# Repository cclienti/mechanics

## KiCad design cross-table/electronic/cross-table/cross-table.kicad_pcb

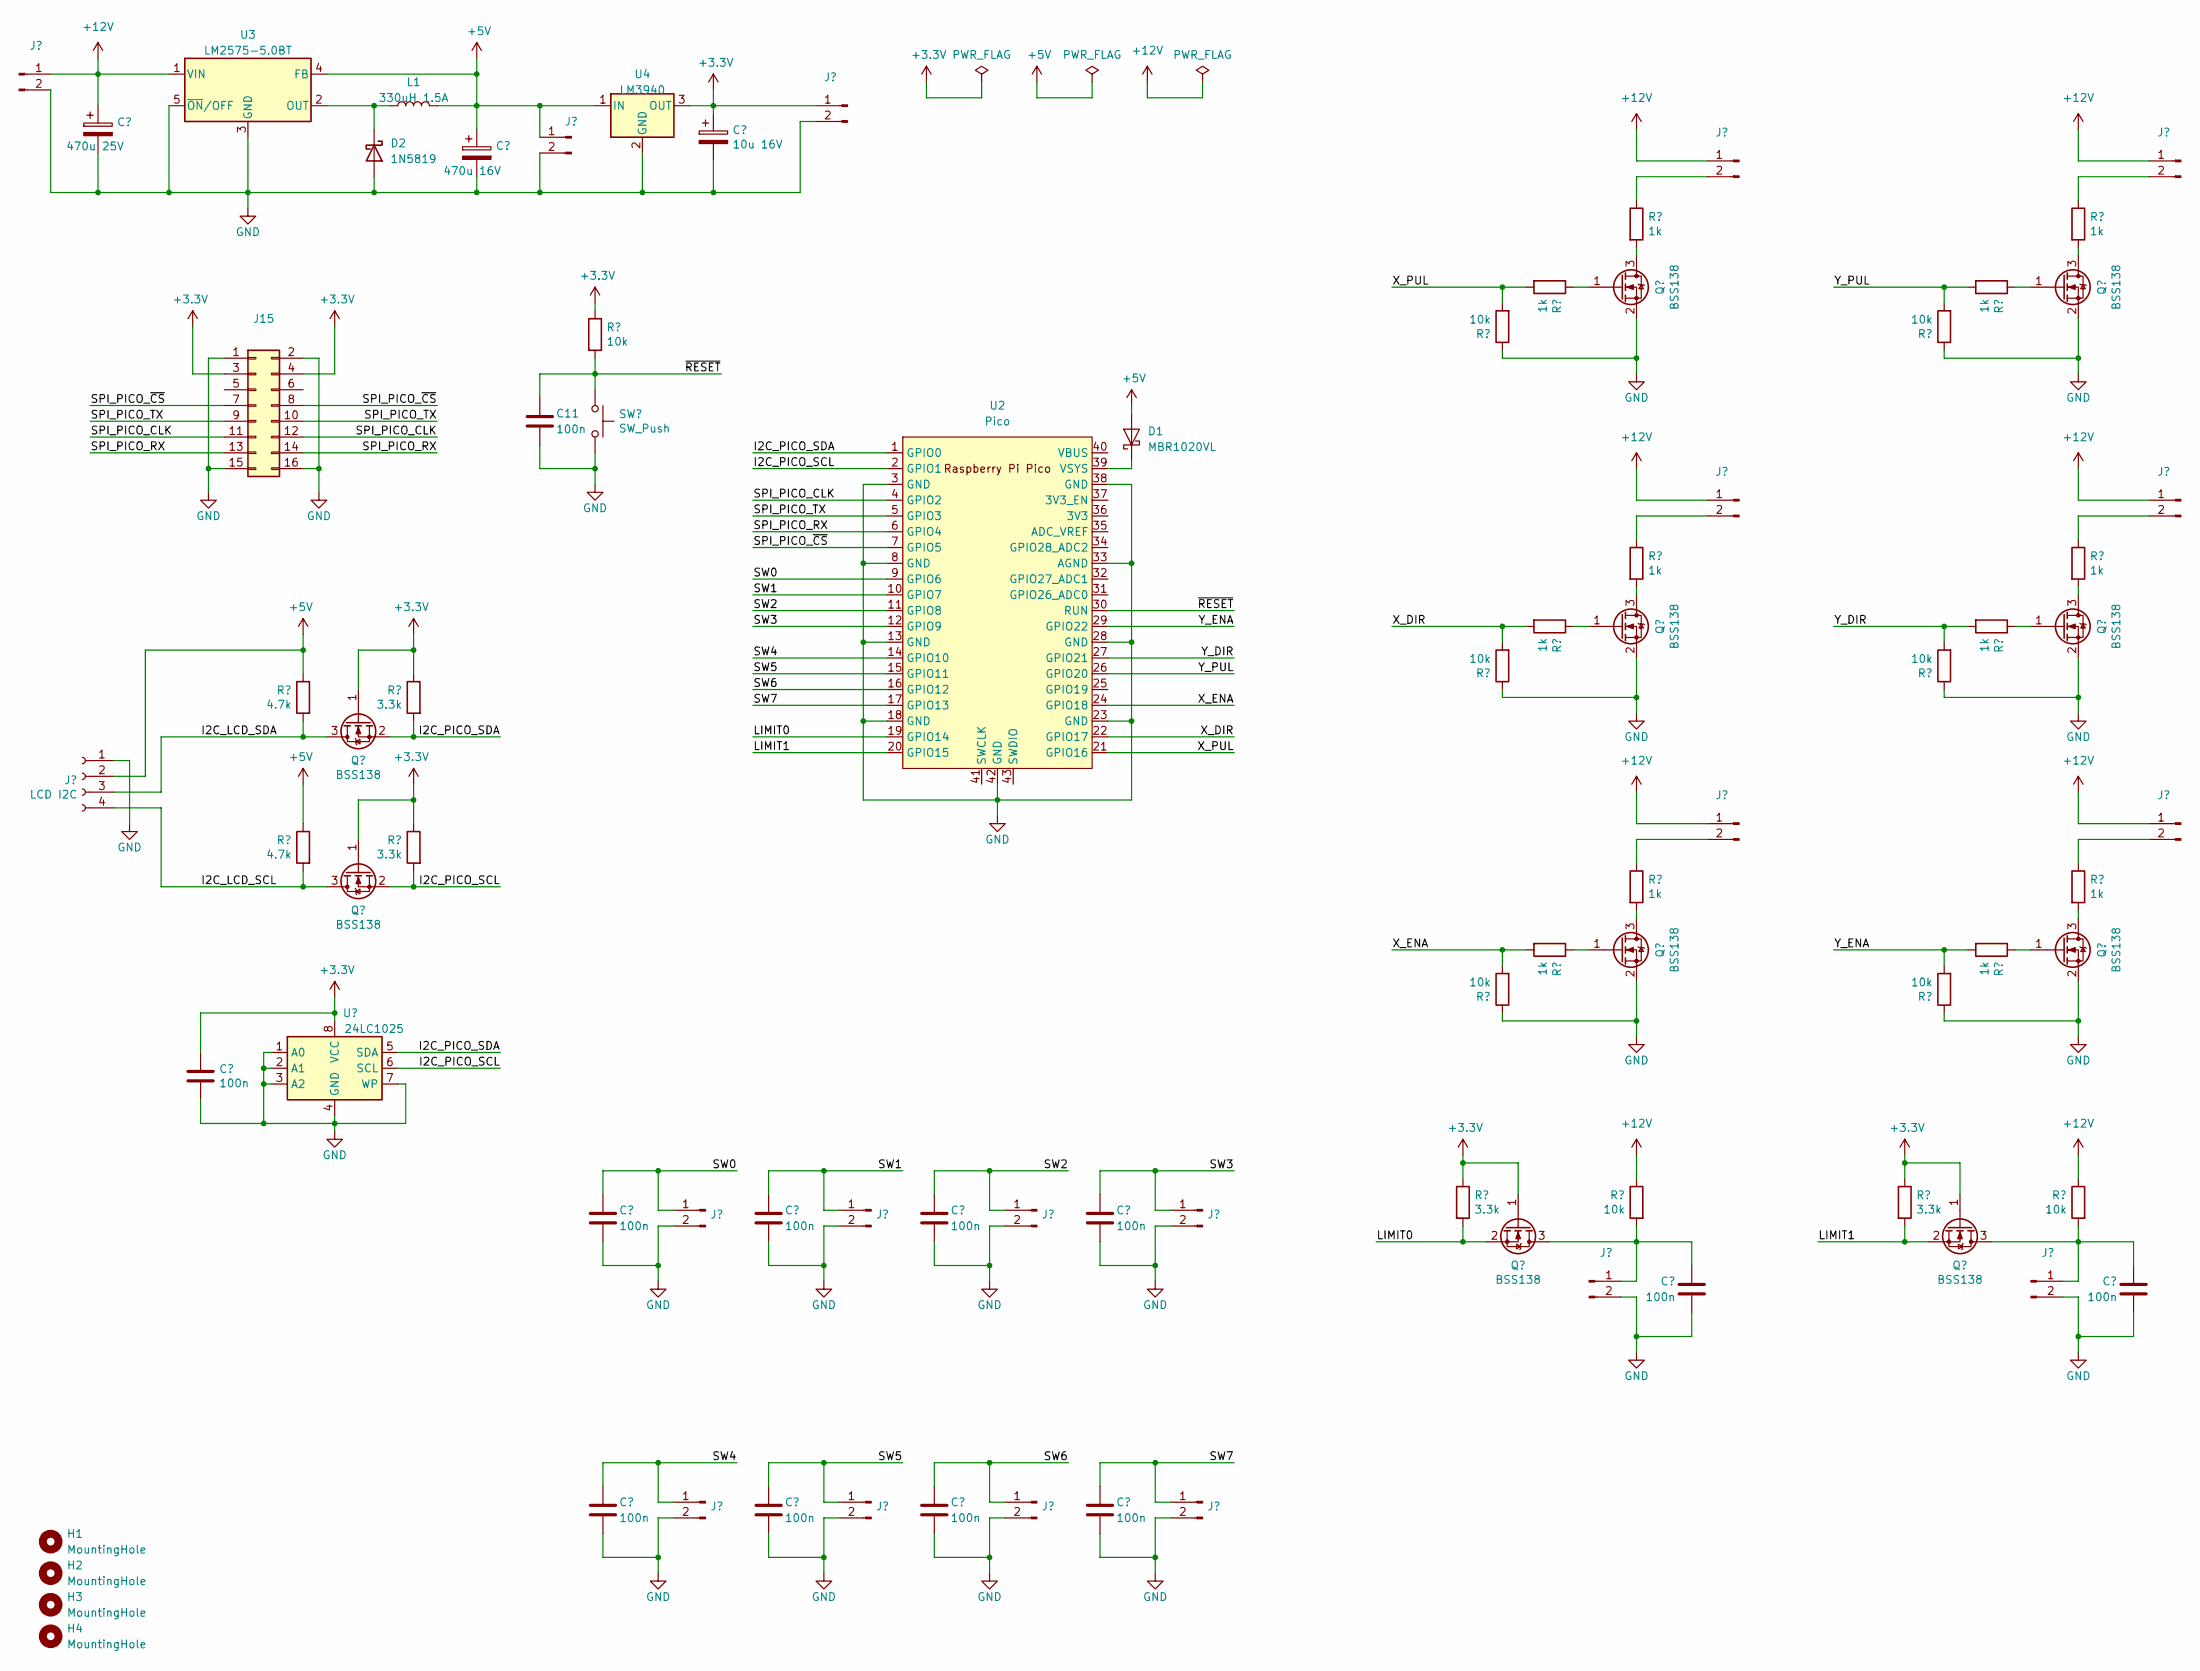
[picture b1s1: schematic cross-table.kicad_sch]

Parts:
C2, C3, C4, C5, C6, C7, C8, C9, C10, C11, C12, C13: 100n; C_1206_3216Metric_Pad1.33x1.80mm_HandSolder
C15: 10u 16V; C_1210_3225Metric_Pad1.33x2.70mm_HandSolder
C16: 470u 16V; CP_Elec_10x10.5
C17: 470u 25V; CP_Elec_10x10.5
D1: MBR1020VL; D_SMA
D2: 1N5819; D_DO-41_SOD81_P10.16mm_Horizontal
H1, H2, H3, H4: MountingHole; MountingHole_3mm_Pad
J1, J11, J12, J13, J14, J16, J17, J18, J19, J20, J21: Conn_01x02_Male; PhoenixContact_MSTBVA_2,5_2-G-5,08_1x02_P5.08mm_Vertical
J2: LCD I2C; PinHeader_1x04_P2.54mm_Vertical
J3, J4, J5, J6, J7, J8, J9, J10: Conn_01x02_Male; PinHeader_1x02_P2.54mm_Vertical
J15: Conn_02x08_Odd_Even; IDC-Header_2x08_P2.54mm_Vertical
L1: 330uH 1.5A; L_12x12mm_H8mm
Q1, Q2, Q3, Q4, Q5, Q6, Q7, Q8, Q9, Q10: BSS138; SOT-23_Handsoldering
R1, R4, R9, R21, R22, R23, R27, R30, R33: 10k; R_1206_3216Metric_Pad1.30x1.75mm_HandSolder
R2, R3, R7, R8, R10, R26, R28, R29, R31, R32, R34, R35: 1k; R_1206_3216Metric_Pad1.30x1.75mm_HandSolder
R5, R6, R24, R25: 3.3k; R_1206_3216Metric_Pad1.30x1.75mm_HandSolder
R11, R12: 4.7k; R_1206_3216Metric_Pad1.30x1.75mm_HandSolder
SW1: SW_Push; SW_PUSH_6mm_H5mm
U1: 24LC1025; DIP-8_W7.62mm
U2: Pico; RPi_Pico_SMD_TH
U3: LM2575-5.0BT; TO-220-5_Vertical
U4: LM3940; TO-220-3_Vertical

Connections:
+3V3: C2.1, C15.1, J15.3, J15.4, J21.1, Q5.1 (G), Q6.1 (G), Q7.1 (G), Q8.1 (G), R5.1, R6.1, R21.1, R24.1, R25.1, U1.8 (VCC), U4.3 (OUT)
+5V: C16.1, D1.2 (A), J2.2, J13.1, L1.2, R11.1, R12.1, U3.4 (FB), U4.1 (IN)
+12V: C17.1, J1.1, J14.1, J16.1, J17.1, J18.1, J19.1, J20.1, R22.1, R23.1, U3.1 (VIN)
/I2C_LCD_SCL: J2.4, Q6.3 (D), R12.2
/I2C_LCD_SDA: J2.3, Q5.3 (D), R11.2
/I2C_PICO_SCL: Q6.2 (S), R6.2, U1.6 (SCL), U2.2 (GPIO1)
/I2C_PICO_SDA: Q5.2 (S), R5.2, U1.5 (SDA), U2.1 (GPIO0)
/LIMIT0: Q7.2 (S), R24.2, U2.19 (GPIO14)
/LIMIT1: Q8.2 (S), R25.2, U2.20 (GPIO15)
/SPI_PICO_CLK: J15.11, J15.12, U2.4 (GPIO2)
/SPI_PICO_RX: J15.13, J15.14, U2.6 (GPIO4)
/SPI_PICO_TX: J15.9, J15.10, U2.5 (GPIO3)
/SPI_PICO_~CS: J15.7, J15.8, U2.7 (GPIO5)
/SW0: C4.1, J4.1, U2.9 (GPIO6)
/SW1: C6.1, J6.1, U2.10 (GPIO7)
/SW2: C8.1, J8.1, U2.11 (GPIO8)
/SW3: C10.1, J10.1, U2.12 (GPIO9)
/SW4: C3.1, J3.1, U2.14 (GPIO10)
/SW5: C5.1, J5.1, U2.15 (GPIO11)
/SW6: C7.1, J7.1, U2.16 (GPIO12)
/SW7: C9.1, J9.1, U2.17 (GPIO13)
/X_DIR: R4.2, R7.2, U2.22 (GPIO17)
/X_ENA: R30.2, R31.2, U2.24 (GPIO18)
/X_PUL: R27.2, R28.2, U2.21 (GPIO16)
/Y_DIR: R9.2, R10.2, U2.27 (GPIO21)
/Y_ENA: R33.2, R34.2, U2.29 (GPIO22)
/Y_PUL: R1.2, R2.2, U2.26 (GPIO20)
/~RESET: C11.1, R21.2, SW1.1, U2.30 (RUN)
GND: C2.2, C3.2, C4.2, C5.2, C6.2, C7.2, C8.2, C9.2, C10.2, C11.2, C12.2, C13.2, C15.2, C16.2, C17.2, D2.2 (A), J1.2, J2.1, J3.2, J4.2, J5.2, J6.2, J7.2, J8.2, J9.2, J10.2, J11.2, J12.2, J13.2, J15.1, J15.2, J15.15, J15.16, J21.2, Q1.2 (S), Q2.2 (S), Q3.2 (S), Q4.2 (S), Q9.2 (S), Q10.2 (S), R1.1, R4.1, R9.1, R27.1, R30.1, R33.1, SW1.2, U1.1 (A0), U1.2 (A1), U1.3 (A2), U1.4 (GND), U1.7 (WP), U2.3 (GND), U2.8 (GND), U2.13 (GND), U2.18 (GND), U2.23 (GND), U2.28 (GND), U2.33 (AGND), U2.38 (GND), U2.42 (GND), U3.3 (GND), U3.5 (~ON/OFF), U4.2 (GND)
unnamed: D1.1 (K), U2.39 (VSYS)
unnamed: D2.1 (K), L1.1, U3.2 (OUT)
unnamed: C13.1, J11.1, Q8.3 (D), R23.2
unnamed: C12.1, J12.1, Q7.3 (D), R22.2
unnamed: J14.2, R26.1
unnamed: J16.2, R3.1
unnamed: J17.2, R8.1
unnamed: J18.2, R29.1
unnamed: J19.2, R32.1
unnamed: J20.2, R35.1
unnamed: Q1.3 (D), R3.2
unnamed: Q1.1 (G), R2.1
unnamed: Q2.3 (D), R8.2
unnamed: Q2.1 (G), R7.1
unnamed: Q3.3 (D), R29.2
unnamed: Q3.1 (G), R10.1
unnamed: Q4.3 (D), R32.2
unnamed: Q4.1 (G), R31.1
unnamed: Q9.3 (D), R26.2
unnamed: Q9.1 (G), R28.1
unnamed: Q10.3 (D), R35.2
unnamed: Q10.1 (G), R34.1

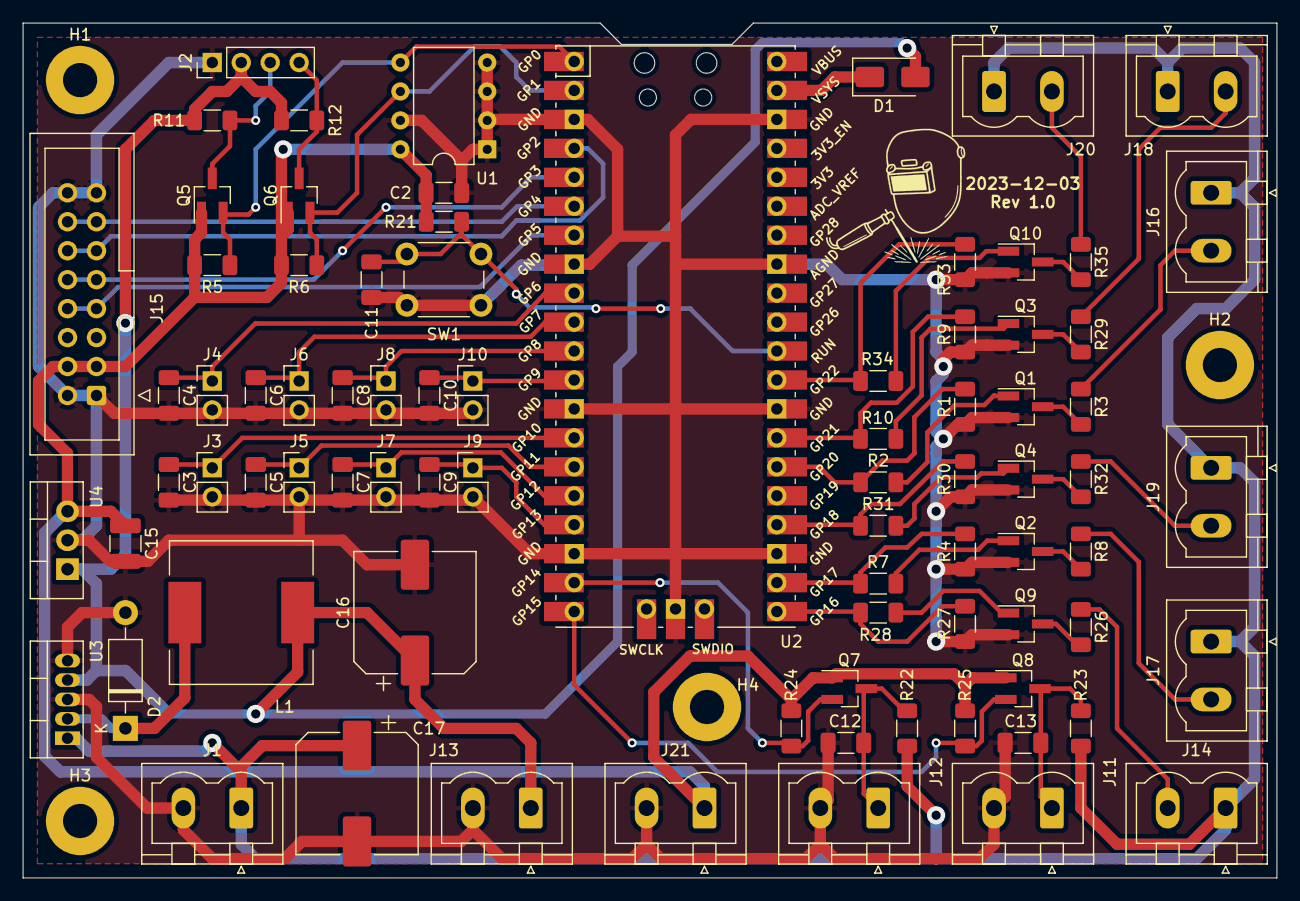
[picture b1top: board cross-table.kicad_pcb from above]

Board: 2 copper layers, 110.0 x 75.0 mm, 85 parts (0 on the bottom side), 51 nets.

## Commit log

2020-10-28 Added the first part and the Makefile to produce DXF
2021-11-26 Updated welding cube dimensions
2021-11-26 Added the welding table
2021-11-26 Added Ironworks directory
2021-11-26 Added the NopSCADlib library as a submodule
2021-11-27 Added the cnc directory
2021-11-27 Added some datasheets
2021-12-04 Added SBR rails
2021-12-04 Added the scr bearing block definition and implementation
2021-12-04 Added cutting cart
2021-12-04 Added the SFU1605 using the leadscrew from NopSCADlib
2021-12-04 Added BK/BF fixed bearing
2021-12-04 Added the Ballscrew Mount
2021-12-04 Moved in a separate directory the CNC parts
2021-12-07 Fixed dimension declarations of bearings
2021-12-07 Added the nema 23 mount adapter
2021-12-07 Added the plasma torch adapter
2021-12-07 Added the nema and torch adapters
2022-01-29 Added the brasero schematics and octagon faces
2022-09-24 Initial plasma cutter main scad file
2022-09-25 Added EK/EF support unit datasheets
2022-09-27 Added SBR20 unit
2022-10-01 Improved BKxx design
2022-10-02 Update plasma cnc design
2023-10-17 Enhancing the cnc axis and normalize length to ease the sourcing
2023-10-18 Added terminal plate to mount nema23 on Y axis
2023-10-19 Added reinforcement bars in the X axis
2023-10-19 Added some a document about computation of arc length in a circle
2023-10-20 Added the metal sheet support for the cnc project.
2023-10-22 Moved leg & plate into a separate module to ease projections
2023-10-24 Added the projections script for the cnc project
2023-10-24 Reworked the projection script to use FreeCAD to produce DXF
    FreeCAD is able to produce DXF with true cirules (ie not approximated by
    lines).
2023-10-26 Added the torche
2023-10-27 Created cnc Z-axis component
2023-10-28 cnc: Added the plate to support the Z-axis
2023-10-29 Reworked cnc projections script input/output directories
2023-10-29 Moved the cnc z-axis mounting plate into a separate file
2023-10-29 Fixed chamfer in cnc plate.scad
2023-10-29 Increased width cnc z-axis mounting plate
2023-10-29 Reworked the torche adapter for the new cnc z-axis
2023-11-01 Added the torche adapter and the torche to the cnc z-axis
2023-11-01 Improved cnc rendering script to move also the z-axis
2023-11-03 Added NEMA23 mounting schematics
2023-11-04 Added the cross-table project for drill press
2023-11-05 cross-table: Added the Y to X interconnection plate
2023-11-09 cnc: improved mounting hole position of sbr rails
2023-11-09 cross-table: added sfu1605 and bf/bk12 on the X layer
2023-11-10 cross-table: added mounting hole in the X to Y plate
2023-11-11 Added specific plates to reinforce the structure
2023-11-12 cross-table: extended X-axis sbr length by 50mm
2023-11-13 cross-table: added leadnut and sbr16uu to the x-axis
2023-11-14 cross-table: added layer x connector
2023-11-15 cross-table: enhanced the top support
2023-11-17 cross-table: added holes in the layer_x_connector
2023-11-17 cross-table: Added a margin to reduce the profile_connector by 1mm
2023-11-17 cross-table: removed rounded corners in layer_y_to_x
2023-11-19 cross-table: added the openscad projection directive
2023-11-21 cross-table: removed holes outside the layer_y_to_x plate
2023-11-21 cross-table: improved the dxf projection script to get only the 2D part
2023-11-21 cnc: backported the projection script from the cross-table project
2023-11-25 cross-table: moved hardware in a dedicated dir
2023-12-03 cross-table: added the electronic board skeleton with RPI pico
2023-12-03 Bumped to KiCad-RP-Pico submodule to last version to fix drill diam
2023-12-22 cross-table: added initial firmware pi-pico C++ project
2023-12-22 firmware: added raspberry pico scripts and sdk submodule
2023-12-25 cross-table: added the stepper motor firmware class
2024-05-09 Moved all pin numbering and constants in a dedicated header file
2024-05-09 cross-table: added support for long press of buttons
2024-06-02 cross-table: handle properly reset button
2024-06-08 Added a tripod plate for for three iron props and a lifting hoist.
2024-06-09 Added the lifting plate for the manual plasma cutter table
2024-06-30 cross-table: handle limit switch during motor rotation
2024-06-30 [cross-table][fw] Moved Buttons class in a separate file
2024-06-30 [cross-table][fw] Added support for sdcard access
2024-06-30 [cross-table][fw] Removed out-dated FatFs_SPI sdcard library
2024-06-30 [cross-table][fw] Switched to the new FatFS sdcard libray
2024-07-18 [scripts] update build picoprobe openocd script
2024-07-18 [manual-cutting-table][meca] added the lifting plate schematics
2024-07-18 [cross-table][fw] fixed .clangd config file for arm-none-eabi toolchain
2024-07-18 [cross-table][fw] fixed missing license header in source files
2024-07-18 [cross-table][fw] Changed order between relative and absolute pos display
2024-07-18 [cross-table][fw] Cleaned compile warning exception in CMakeLists.txt
2024-07-18 [cross-table][fw] Added the support of a menu generic dialog in LCDMenu
2024-07-18 [woodworks] added the Z shutter scad file
2025-03-02 [cross-table][fw] added support for sdcard coordinates reading
2025-03-02 [cross-table][fw] added a method to get the list of files in root of sdcard
2025-03-02 [woodworks] Updated shutter dimensions
2025-03-02 [cross-table][fw] Handle precision at half a tenth of millimeter
2025-03-02 [cross-table][fw] Improved precision axis display
2025-03-02 [cross-table][fw] Fixed positions rollbacks and added holes on circle
2025-03-02 [cross-table][fw] cleaned method naming in lcd_menu for dialog management
2025-03-02 [cross-table][fw] Added an item selection system in the menu
2025-03-02 [cross-table][fw] Handle the cross-table position update and rollback.
    A generic system has been implemented: when a sdcard data is loaded or
    when a "holes on a line" generator is used, a vector of PulseUpdate is
    created.
    The main position menu handles the vector of PulseUpdate to give the
    possibility to the user to move the table or rollback it at each
    step (ie for each PulseUpdate in the vector).
2025-03-02 [cross-table][fw] Improved unit tests
2025-03-02 [cross-table][fw] Disable dry-run and hold motor until position changed by the user
2025-03-02 [cross-table][fw] Added the menu to load from SD and use the SDCardReader
2025-03-02 [cross-table][fw] Bumped pico-sdk & no-OS-FatFS-SD-SDIO-SPI-RPi-Pico submodules
2025-04-17 [cross-table][fw] added the holes on grid function
